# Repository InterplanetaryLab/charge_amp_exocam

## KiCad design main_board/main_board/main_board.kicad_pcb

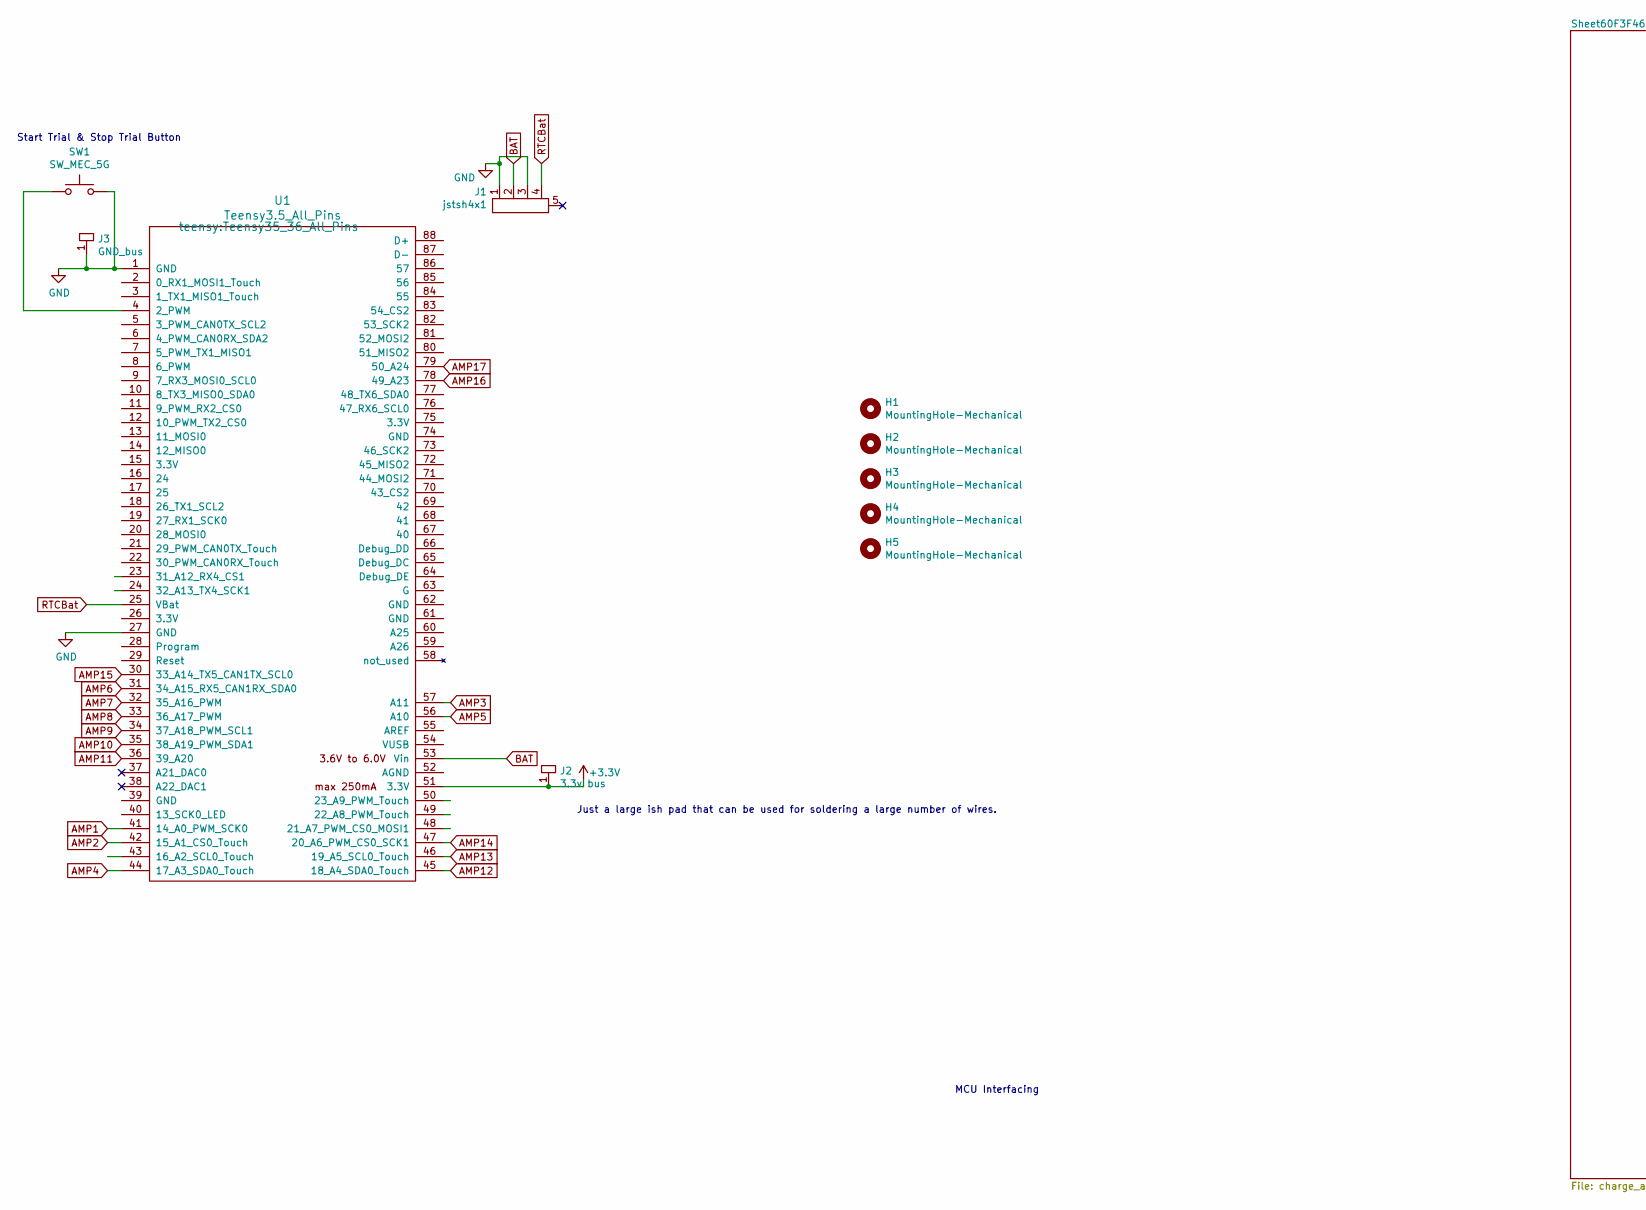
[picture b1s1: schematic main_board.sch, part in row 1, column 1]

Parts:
H1, H2, H3, H4: MountingHole-Mechanical; mount_hole_3mm
H5: MountingHole-Mechanical; mount_hole_2.5mm
J1: jstsh4x1
J2: 3.3v bus; power_bus
J3: GND_bus; power_bus
SW1: SW_MEC_5G
U1: Teensy3.5_All_Pins; Teensy35_36_All_Pins

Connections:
+3V3: J2.1, U1.51 (3.3V); also elsewhere on the board
AMP1: U1.41 (14_A0_PWM_SCK0)
AMP2: U1.42 (15_A1_CS0_Touch)
AMP3: U1.57 (A11)
AMP4: U1.44 (17_A3_SDA0_Touch)
AMP5: U1.56 (A10)
AMP6: U1.31 (34_A15_RX5_CAN1RX_SDA0)
AMP7: U1.32 (35_A16_PWM)
AMP8: U1.33 (36_A17_PWM)
AMP9: U1.34 (37_A18_PWM_SCL1)
AMP10: U1.35 (38_A19_PWM_SDA1)
AMP11: U1.36 (39_A20)
AMP12: U1.45 (18_A4_SDA0_Touch)
AMP13: U1.46 (19_A5_SCL0_Touch)
AMP14: U1.47 (20_A6_PWM_CS0_SCK1)
AMP15: U1.30 (33_A14_TX5_CAN1TX_SCL0); also elsewhere on the board
AMP16: U1.78 (49_A23); also elsewhere on the board
AMP17: U1.79 (50_A24); also elsewhere on the board
BAT: J1.2, U1.53 (Vin)
GND: J1.1, J1.3, J3.1, SW1.3 (B), SW1.4 (B), U1.1 (GND), U1.27 (GND); also elsewhere on the board
unnamed: SW1.1 (A), SW1.2 (A), U1.4 (2_PWM)
RTCBat: J1.4, U1.25 (VBat)

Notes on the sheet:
MCU Interfacing
Just a large ish pad that can be used for soldering a large number of wires.
Start Trial & Stop Trial Button

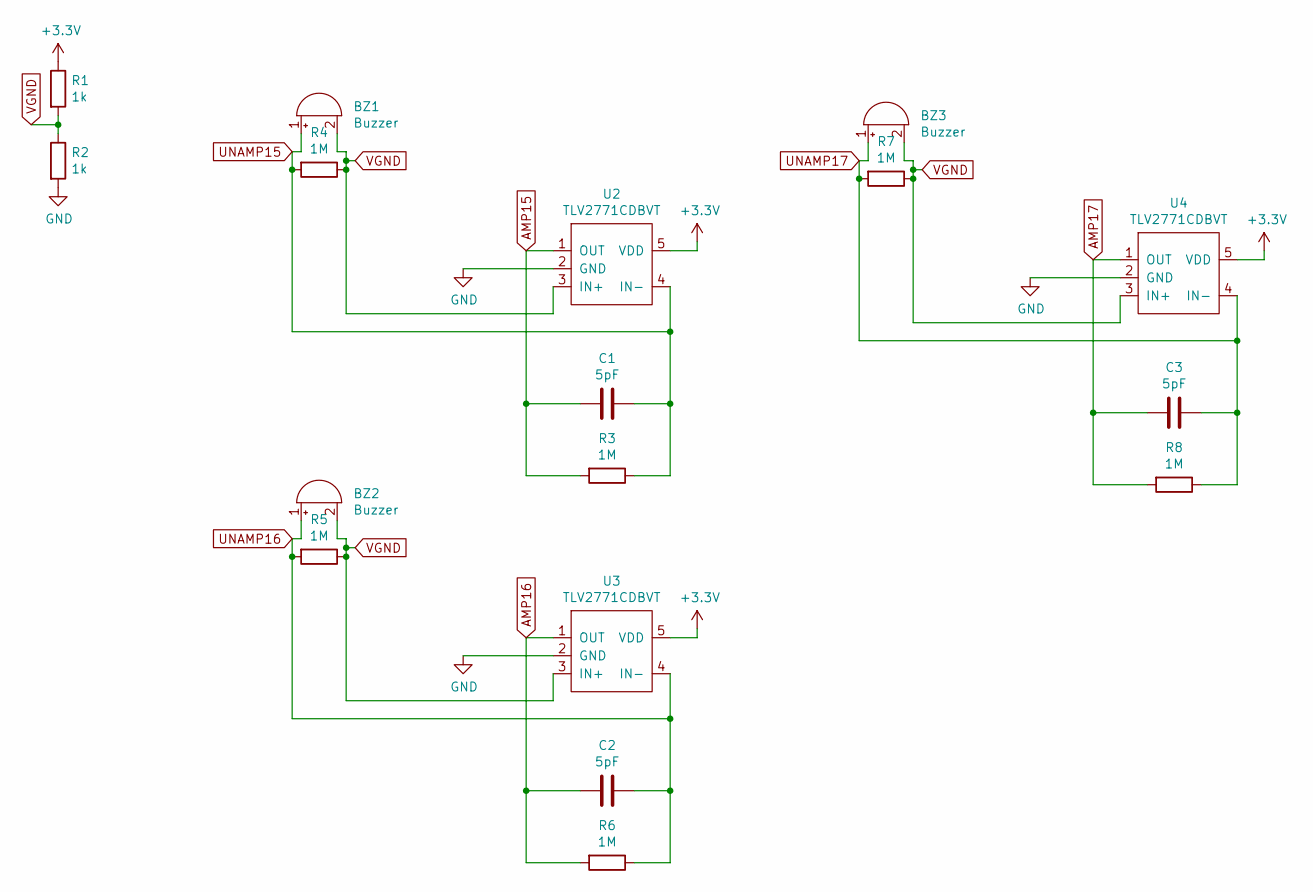
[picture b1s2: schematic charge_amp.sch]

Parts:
BZ1, BZ2, BZ3: Buzzer; piezo_buzzer_alt
C1, C2, C3: 5pF; 0603_R
R1, R2: 1k; 0603_R
R3, R4, R5, R6, R7, R8: 1M; 0603_R
U2, U3, U4: TLV2771CDBVT; TLV2271DBV

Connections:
+3V3: R1.1, U2.5 (VDD), U3.5 (VDD), U4.5 (VDD); also elsewhere on the board
AMP15: C1.2, R3.2, U2.1 (OUT); also elsewhere on the board
AMP16: C2.2, R6.2, U3.1 (OUT); also elsewhere on the board
AMP17: C3.2, R8.2, U4.1 (OUT); also elsewhere on the board
GND: R2.2, U2.2 (GND), U3.2 (GND), U4.2 (GND); also elsewhere on the board
UNAMP15: BZ1.1 (-), C1.1, R3.1, R4.2, U2.4 (IN-)
UNAMP16: BZ2.1 (-), C2.1, R5.2, R6.1, U3.4 (IN-)
UNAMP17: BZ3.1 (-), C3.1, R7.2, R8.1, U4.4 (IN-)
VGND: BZ1.2 (+), BZ2.2 (+), BZ3.2 (+), R1.2, R2.1, R4.1, R5.1, R7.1, U2.3 (IN+), U3.3 (IN+), U4.3 (IN+)

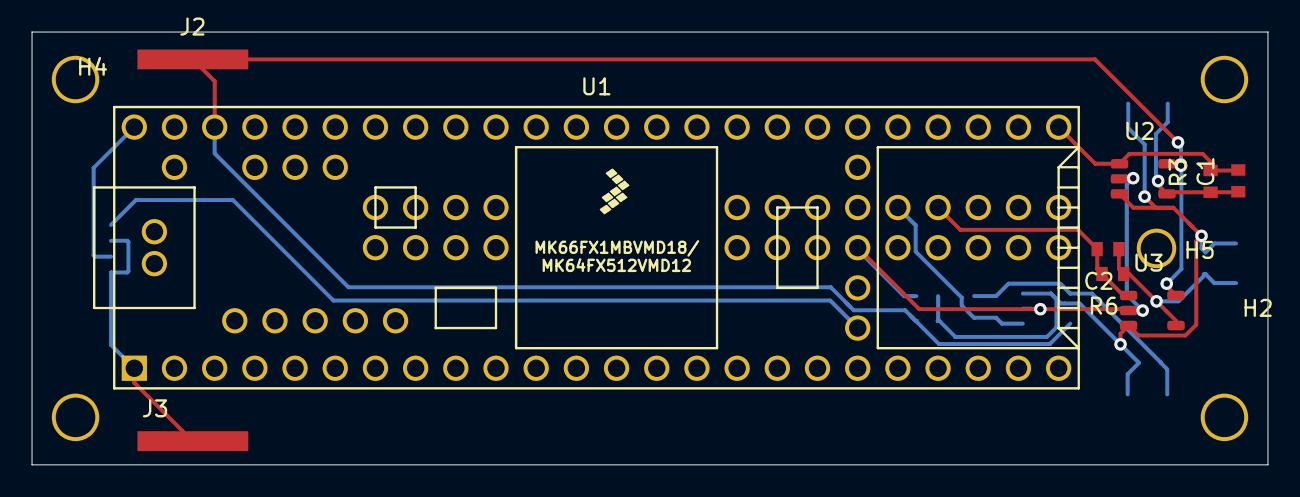
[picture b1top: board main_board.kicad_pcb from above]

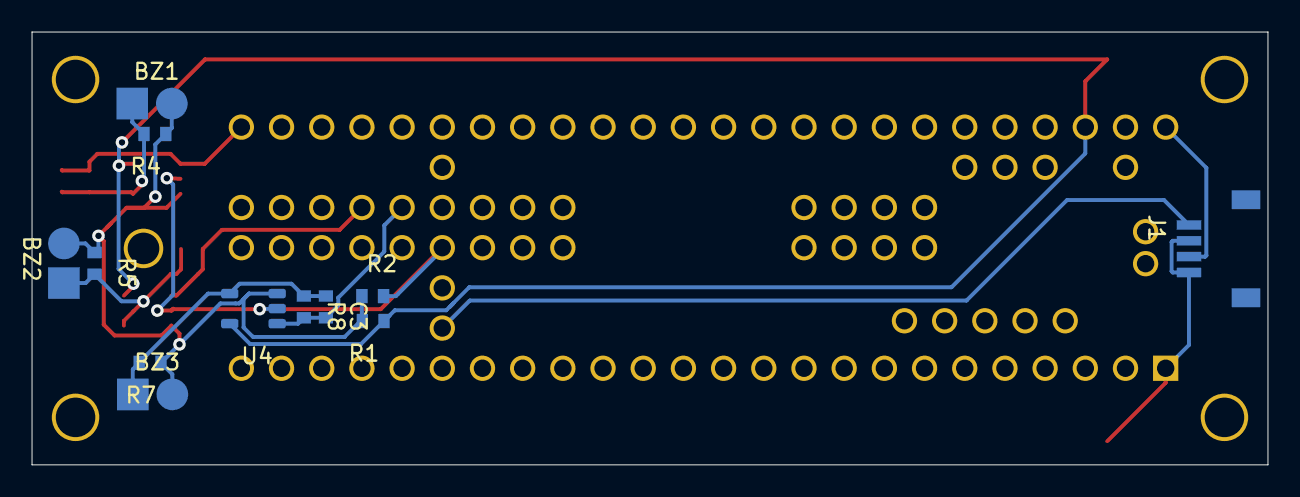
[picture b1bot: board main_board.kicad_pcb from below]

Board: 2 copper layers, 78.1 x 27.4 mm, 26 parts (12 on the bottom side), 11 nets.

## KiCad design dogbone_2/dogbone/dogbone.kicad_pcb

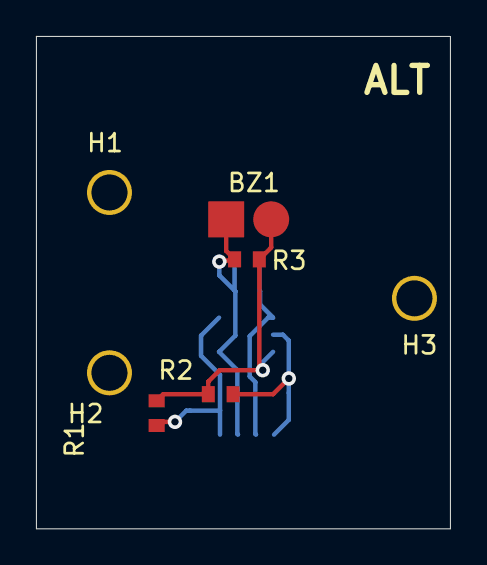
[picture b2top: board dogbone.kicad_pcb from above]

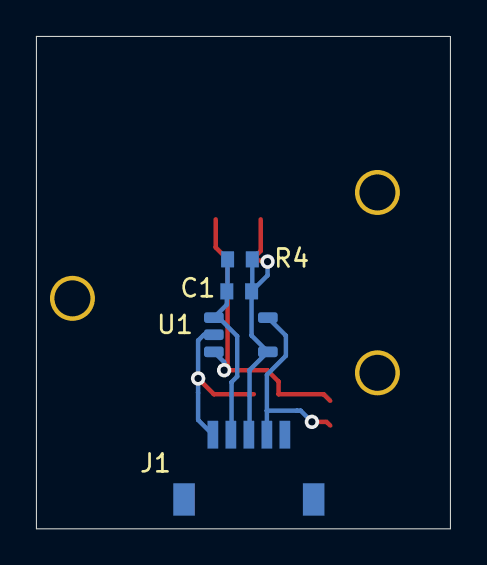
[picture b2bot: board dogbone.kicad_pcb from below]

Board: 2 copper layers, 23.0 x 27.4 mm, 11 parts (4 on the bottom side), 5 nets.

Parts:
BZ1: Buzzer; piezo_buzzer_alt
C1: 5pF; 0603_R
H1, H2, H3: MountingHole; mount_hole_2.5mm
J1: jstsh5x1
R1, R2: 1k; 0603_R
R3, R4: 1M; 0603_R
U1: TLV2771CDBVT; TLV2271DBV

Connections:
+3V3: J1.4, R1.1, U1.5
AMP: C1.2, J1.2, R4.2, U1.1
GND: J1.1, R2.2, U1.2
UNAMP: BZ1.1, C1.1, J1.3, R3.2, R4.1, U1.4
VGND: BZ1.2, R1.2, R2.1, R3.1, U1.3

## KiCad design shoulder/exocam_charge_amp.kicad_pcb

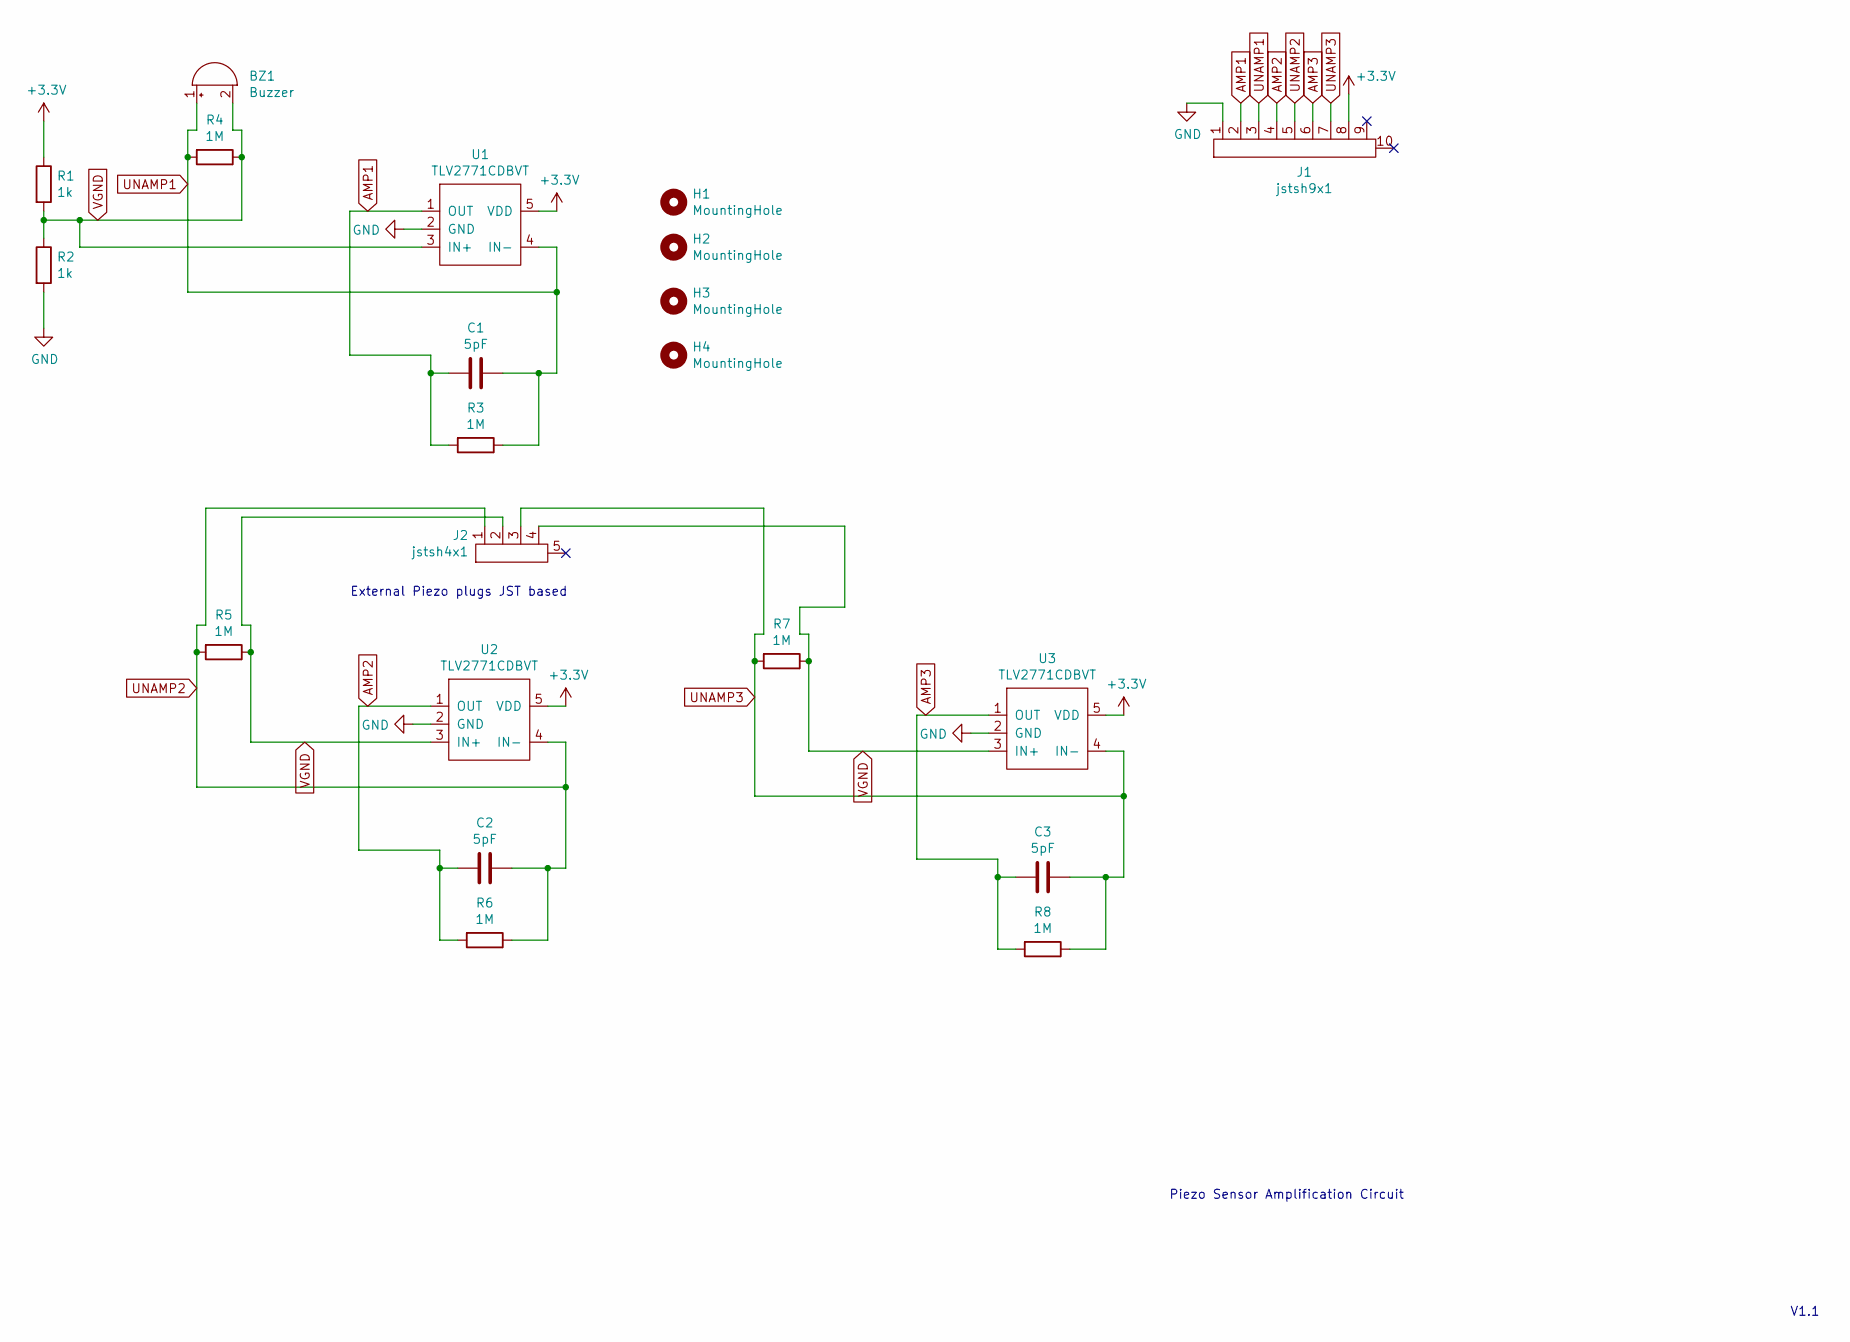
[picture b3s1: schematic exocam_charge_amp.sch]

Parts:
BZ1: Buzzer; piezo_buzzer_alt
C1, C2, C3: 5pF; 0603_R
H1, H2, H3, H4: MountingHole; mount_hole_2.5mm
J1: jstsh9x1
J2: jstsh4x1
R1, R2: 1k; 0603_R
R3, R4, R5, R6, R7, R8: 1M; 0603_R
U1, U2, U3: TLV2771CDBVT; TLV2271DBV

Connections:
+3V3: J1.8, R1.1, U1.5 (VDD), U2.5 (VDD), U3.5 (VDD)
AMP1: C1.2, J1.2, R3.2, U1.1 (OUT)
AMP2: C2.2, J1.4, R6.2, U2.1 (OUT)
AMP3: C3.2, J1.6, R8.2, U3.1 (OUT)
GND: J1.1, R2.2, U1.2 (GND), U2.2 (GND), U3.2 (GND)
UNAMP1: BZ1.1 (-), C1.1, J1.3, R3.1, R4.2, U1.4 (IN-)
UNAMP2: C2.1, J1.5, J2.1, R5.2, R6.1, U2.4 (IN-)
UNAMP3: C3.1, J1.7, J2.3, R7.2, R8.1, U3.4 (IN-)
VGND: BZ1.2 (+), J2.2, J2.4, R1.2, R2.1, R4.1, R5.1, R7.1, U1.3 (IN+), U2.3 (IN+), U3.3 (IN+)

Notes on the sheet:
Piezo Sensor Amplification Circuit
V1.1
External Piezo plugs JST based

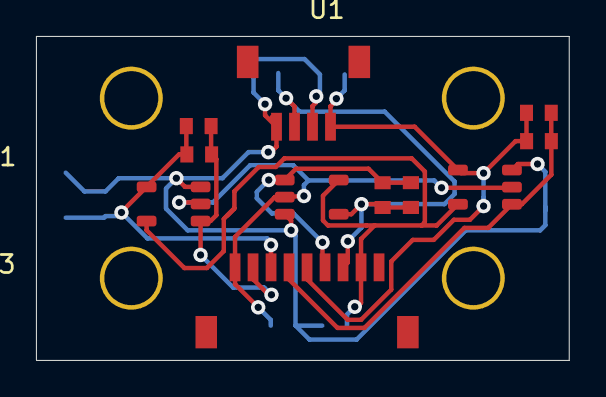
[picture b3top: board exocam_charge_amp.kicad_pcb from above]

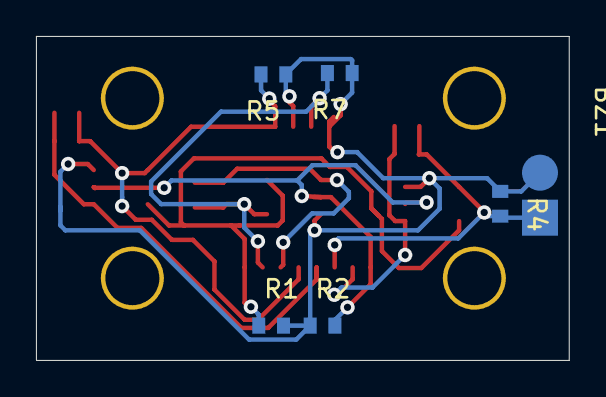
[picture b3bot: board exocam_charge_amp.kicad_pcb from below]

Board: 2 copper layers, 29.6 x 18.0 mm, 21 parts (6 on the bottom side), 9 nets.

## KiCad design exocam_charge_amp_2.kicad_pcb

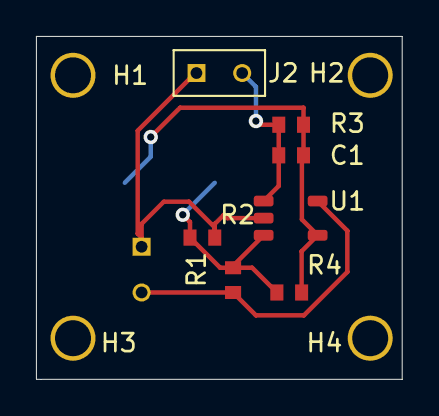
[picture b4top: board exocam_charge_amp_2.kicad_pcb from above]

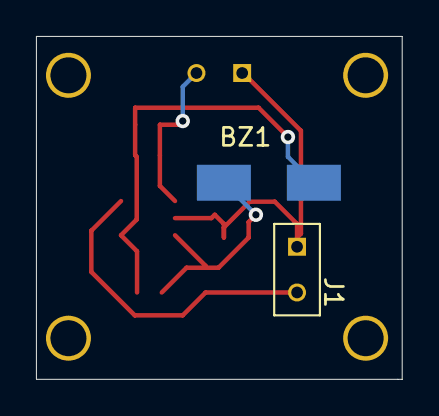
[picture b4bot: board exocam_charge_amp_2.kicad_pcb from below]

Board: 2 copper layers, 20.3 x 19.0 mm, 13 parts (2 on the bottom side), 5 nets.

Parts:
BZ1: Buzzer; piezo_buzzer
C1: 5pF; 0603_R
H1, H2, H3, H4: MountingHole; mount_hole_2.5mm
J1, J2: dupont2x1
R1, R2: 1k; 0603_R
R3, R4: 1M; 0603_R
U1: TLV2771CDBVT; TLV2271DBV

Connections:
+5V: J1.2, R1.1, U1.5
GND: J1.1, J2.1, R2.2, U1.2
unnamed: BZ1.1, C1.1, R3.1, R4.2, U1.4
unnamed: BZ1.2, R1.2, R2.1, R4.1, U1.3
unnamed: C1.2, J2.2, R3.2, U1.1

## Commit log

2021-05-25 inital commit of charge amp circuit
2021-05-25 added pictures and schematic export to a pdf for easier viewability
2021-05-25 added step and updated to have screw mounts for the board
2021-05-25 added output terminals
2021-05-26 fixed ground trace
2021-05-27 stl with pads export
2021-06-29 updated pcb to be the new hole pattern on the shoulder side
2021-06-29 modify board to be the two way amplification stage for higher range of outputs
2021-06-30 latest update of design
2021-06-30 updated so that vertical distance is correct for the holes
2021-06-30 shoulder silkscreen updated
2021-06-30 added step output for shoulder
2021-07-02 updated shoulder board to use the new hole pattern, probably will be redesigned again though
2021-07-02 added jst connector
2021-07-02 updated pcb to mostly reflect double amp
2021-07-06 updated shoulder to include the 3 amps
2021-07-06 refactored so that each board is organized into its own folder
2021-07-06 starting dogbone and more re-organizing
2021-07-14 added main_board
2021-07-14 added more to main board
2021-07-19 added grbl files for dogbone, and update csv
2021-07-20 updated dog bone schematic
2021-07-28 added additional jst connectors
2021-07-28 removed some secondary pcb files for the shoulder (deprecated)
2021-07-28 re-did shoulder board to compensate for lack of connectors
2021-07-29 added more to the mainboard/daugher board
2021-07-29 re added teensy footprints
2021-07-29 updated changes pertaining to daughter board
2021-07-29 some more layouting of the daugher board
2021-07-29 more layout changes for daughter board
2021-07-29 first version of daughter board with pinout
2021-07-29 redid daughter board as the time frame and cost was too much with 4 layers (an not really needed).
2021-08-06 fixed dogbones
2021-08-06 updated grbl files for the dogbones to contain the correct trace routing...
2021-08-06 updated daughter board schematic
2021-08-06 updated daughter board holes, should be good to fab
2021-08-13 adjusting hole patterns
2021-08-13 updated daugherboard to be the latest version
2021-08-13 updated mainboard with correct hole spacing
2021-08-13 added solidworks pdfs for the different layout's hole patterns
2021-08-23 edited daughter board schematic slightly to include the latest push button addition
2021-09-01 updated pinout for daughter board (changed pin for AMP3)
